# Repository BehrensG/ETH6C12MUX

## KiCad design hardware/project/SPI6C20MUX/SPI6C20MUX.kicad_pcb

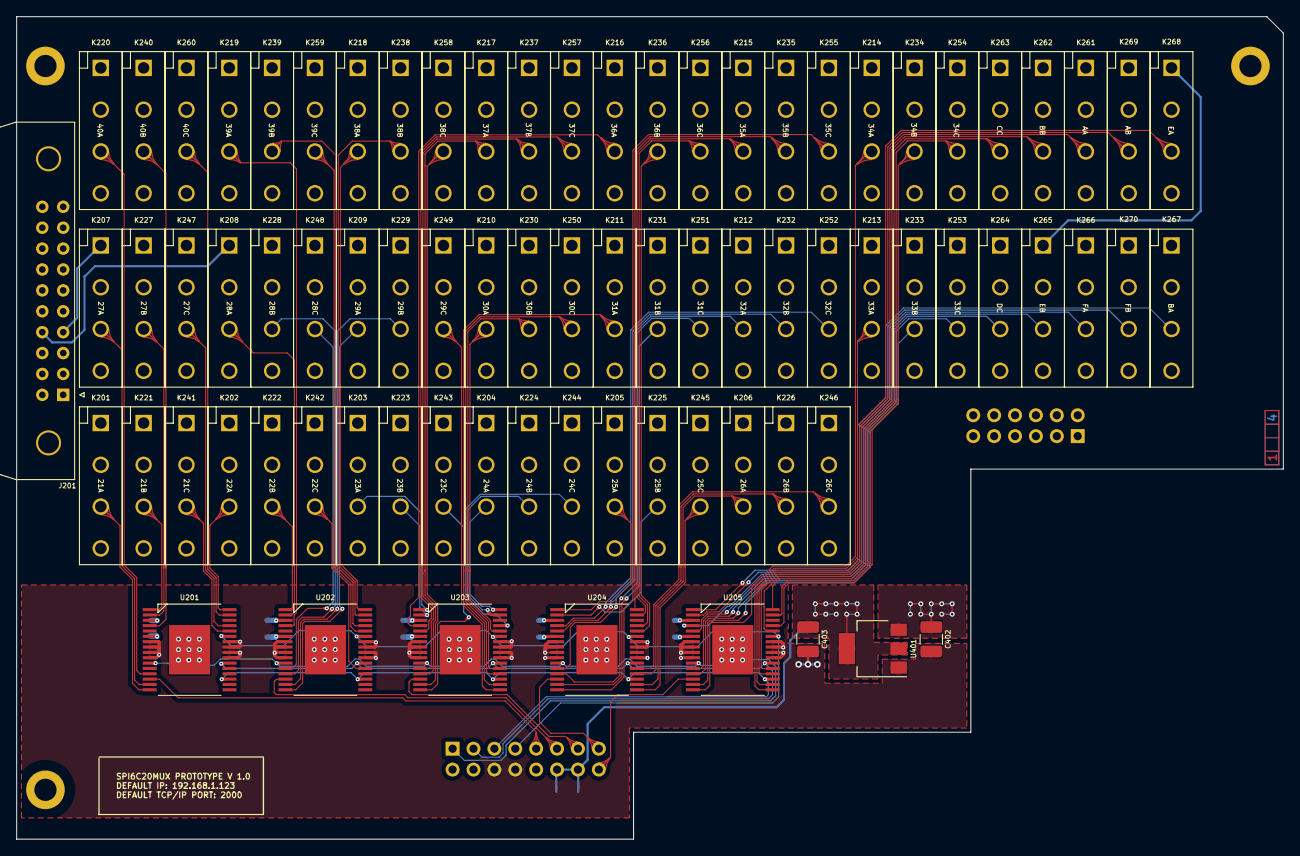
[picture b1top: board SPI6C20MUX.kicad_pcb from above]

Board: 4 copper layers, 154.0 x 100.0 mm, 98 parts (0 on the bottom side), 111 nets.

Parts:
C201, C202, C203, C204, C205, C206, C207, C208, C209, C210, C401, C404: 100n; C_0603_1608Metric_Pad1.05x0.95mm_HandSolder
C402, C403: 22u; C_1210_3225Metric_Pad1.42x2.65mm_HandSolder
H101, H102, H103: MountingHole; MountingHole_2.7mm_M2.5_DIN965_Pad
J201: 5499141-4; IDC-Header_2x10_P2.54mm_Horizontal_Lock
J301: Conn_02x06_Odd_Even; PinHeader_2x06_P2.54mm_Vertical
J302: Conn_02x08_Odd_Even; PinHeader_2x08_P2.54mm_Vertical
K201, K202, K203, K204, K205, K206, K207, K208, K209, K210, K211, K212, K213, K214, K215, K216, K217, K218, K219, K220, K221, K222, K223, K224, K225, K226, K227, K228, K229, K230, K231, K232, K233, K234, K235, K236, K237, K238, K239, K240, K241, K242, K243, K244, K245, K246, K247, K248, K249, K250, K251, K252, K253, K254, K255, K256, K257, K258, K259, K260, K261, K262, K263, K264, K265, K266, K267, K268, K269, K270: HE3621A0510; HE360_x-5331272-5
R301, R302: 10k; R_0603_1608Metric_Pad1.05x0.95mm_HandSolder
U201, U202, U203, U204, U205: MCZ33996; HSOP-32-1EP_7.5x11.0mm_P0.65mm_ThermalVias
U401: LM1117MPX-3.3; SOT-223-3_TabPin2

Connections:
+3V3: C201.1, C202.1, C203.1, C204.1, C205.1, C403.1, C404.1, J302.12, J302.14, R301.1, R302.1, U201.3, U202.3, U203.3, U204.3, U205.3, U401.2
+5V: C206.1, C207.1, C208.1, C209.1, C210.1, C401.1, C402.1, J302.2, J302.4, K201.2, K202.2, K203.2, K204.2, K205.2, K206.2, K207.2, K208.2, K209.2, K210.2, K211.2, K212.2, K213.2, K214.2, K215.2, K216.2, K217.2, K218.2, K219.2, K220.2, K221.2, K222.2, K223.2, K224.2, K225.2, K226.2, K227.2, K228.2, K229.2, K230.2, K231.2, K232.2, K233.2, K234.2, K235.2, K236.2, K237.2, K238.2, K239.2, K240.2, K241.2, K242.2, K243.2, K244.2, K245.2, K246.2, K247.2, K248.2, K249.2, K250.2, K251.2, K252.2, K253.2, K254.2, K255.2, K256.2, K257.2, K258.2, K259.2, K260.2, K261.2, K262.2, K263.2, K264.2, K265.2, K266.2, K267.2, K268.2, K269.2, K270.2, U201.6, U202.6, U203.6, U204.6, U205.6, U401.3
/Connector/A: J301.1, J301.2, K261.1, K269.1
/Connector/B: J301.3, J301.4, K262.1, K267.1
/Connector/C: J301.5, J301.6, K263.1
/Connector/D: J301.11, J301.12, K264.1
/Connector/E: J301.9, J301.10, K265.1, K268.1
/Connector/F: J301.7, J301.8, K266.1, K270.1
/Connector/RELAY2_SCLK: J302.1, U201.11, U202.11, U203.11, U204.11, U205.11
/Connector/RELAY2_SI: J302.5, U201.19, U202.19, U203.19, U204.19, U205.19
/Connector/RELAY2_SO: J302.3, U201.22, U202.22, U203.22, U204.22, U205.22
/Connector/RELAY2_~CS0: J302.9, U201.14
/Connector/RELAY2_~CS1: J302.11, U202.14
/Connector/RELAY2_~CS2: J302.13, U203.14
/Connector/RELAY2_~CS3: J302.15, U204.14
/Connector/RELAY2_~CS4: J302.16, U205.14
/Connector/RELAY2_~RST: J302.7, U201.27, U202.27, U203.27, U204.27, U205.27
/Relays/PIN21: J201.1, K201.1, K221.1, K241.1
/Relays/PIN21A: K201.4, K202.4, K203.4, K204.4, K205.4, K206.4, K207.4, K208.4, K209.4, K210.4, K211.4, K212.4, K213.4, K214.4, K215.4, K216.4, K217.4, K218.4, K219.4, K220.4, K261.4, K266.4, K267.4, K268.4
/Relays/PIN21B: K221.4, K222.4, K223.4, K224.4, K225.4, K226.4, K227.4, K228.4, K229.4, K230.4, K231.4, K232.4, K233.4, K234.4, K235.4, K236.4, K237.4, K238.4, K239.4, K240.4, K262.4, K265.4, K269.4, K270.4
/Relays/PIN21C: K241.4, K242.4, K243.4, K244.4, K245.4, K246.4, K247.4, K248.4, K249.4, K250.4, K251.4, K252.4, K253.4, K254.4, K255.4, K256.4, K257.4, K258.4, K259.4, K260.4, K263.4, K264.4
/Relays/PIN22: J201.2, K202.1, K222.1, K242.1
/Relays/PIN23: J201.3, K203.1, K223.1, K243.1
/Relays/PIN24: J201.4, K204.1, K224.1, K244.1
/Relays/PIN25: J201.5, K205.1, K225.1, K245.1
/Relays/PIN26: J201.6, K206.1, K226.1, K246.1
/Relays/PIN27: J201.7, K207.1, K227.1, K247.1
/Relays/PIN28: J201.8, K208.1, K228.1, K248.1
/Relays/PIN29: J201.9, K209.1, K229.1, K249.1
/Relays/PIN30: J201.10, K210.1, K230.1, K250.1
/Relays/PIN31: J201.11, K211.1, K231.1, K251.1
/Relays/PIN32: J201.12, K212.1, K232.1, K252.1
/Relays/PIN33: J201.13, K213.1, K233.1, K253.1
/Relays/PIN34: J201.14, K214.1, K234.1, K254.1
/Relays/PIN35: J201.15, K215.1, K235.1, K255.1
/Relays/PIN36: J201.16, K216.1, K236.1, K256.1
/Relays/PIN37: J201.17, K217.1, K237.1, K257.1
/Relays/PIN38: J201.18, K218.1, K238.1, K258.1
/Relays/PIN39: J201.19, K219.1, K239.1, K259.1
/Relays/PIN40: J201.20, K220.1, K240.1, K260.1
/Relays/RELAY21A: K201.3, U201.16
/Relays/RELAY21B: K221.3, U201.1
/Relays/RELAY21C: K241.3, U201.28
/Relays/RELAY22A: K202.3, U201.32
/Relays/RELAY22B: K222.3, U202.1
/Relays/RELAY22C: K242.3, U202.21
/Relays/RELAY23A: K203.3, U203.1
/Relays/RELAY23B: K223.3, U203.2
/Relays/RELAY23C: K243.3, U203.16
/Relays/RELAY24A: K204.3, U203.32
/Relays/RELAY24B: K224.3, U203.31
/Relays/RELAY24C: K244.3, U203.29
/Relays/RELAY25A: K205.3, U204.1
/Relays/RELAY25B: K225.3, U204.2
/Relays/RELAY25C: K245.3, U204.17
/Relays/RELAY26A: K206.3, U204.18
/Relays/RELAY26B: K226.3, U204.20
/Relays/RELAY26C: K246.3, U204.21
/Relays/RELAY27A: K207.3, U201.15
/Relays/RELAY27B: K227.3, U201.2
/Relays/RELAY27C: K247.3, U201.29
/Relays/RELAY28A: K208.3, U202.2
/Relays/RELAY28B: K228.3, U202.13
/Relays/RELAY28C: K248.3, U202.12
/Relays/RELAY29A: K209.3, U202.16
/Relays/RELAY29B: K229.3, U202.15
/Relays/RELAY29C: K249.3, U203.17
/Relays/RELAY30A: K210.3, U203.28
/Relays/RELAY30B: K230.3, U203.21
/Relays/RELAY30C: K250.3, U203.20
/Relays/RELAY31A: K211.3, U203.18
/Relays/RELAY31B: K231.3, U204.15
/Relays/RELAY31C: K251.3, U204.13
/Relays/RELAY32A: K212.3, U204.12
/Relays/RELAY32B: K232.3, U204.5
/Relays/RELAY32C: K252.3, U204.4
/Relays/RELAY33A: K213.3, U205.17
/Relays/RELAY33B: K233.3, U205.15
/Relays/RELAY33C: K253.3, U205.13
/Relays/RELAY34A: K214.3, U205.16
/Relays/RELAY34B: K234.3, U205.29
/Relays/RELAY34C: K254.3, U205.31
/Relays/RELAY35A: K215.3, U204.31
/Relays/RELAY35B: K235.3, U204.32
/Relays/RELAY35C: K255.3, U204.16
/Relays/RELAY36A: K216.3, U203.4
/Relays/RELAY36B: K236.3, U204.28
/Relays/RELAY36C: K256.3, U204.29
/Relays/RELAY37A: K217.3, U203.13
/Relays/RELAY37B: K237.3, U203.12
/Relays/RELAY37C: K257.3, U203.5
/Relays/RELAY38A: K218.3, U202.32
/Relays/RELAY38B: K238.3, U202.31
/Relays/RELAY38C: K258.3, U203.15
/Relays/RELAY39A: K219.3, U202.4
/Relays/RELAY39B: K239.3, U202.29
/Relays/RELAY39C: K259.3, U202.28
/Relays/RELAY40A: K220.3, U201.13
/Relays/RELAY40B: K240.3, U201.4
/Relays/RELAY40C: K260.3, U201.31
/Relays/RELAYA: K261.3, U205.21
/Relays/RELAYAB: K269.3, U205.20
/Relays/RELAYB: K262.3, U205.28
/Relays/RELAYBA: K267.3, U205.1
/Relays/RELAYC: K263.3, U205.32
/Relays/RELAYD: K264.3, U205.12
/Relays/RELAYE: K265.3, U205.5
/Relays/RELAYEA: K268.3, U205.18
/Relays/RELAYF: K266.3, U205.4
/Relays/RELAYFA: K270.3, U205.2
GND: C201.2, C202.2, C203.2, C204.2, C205.2, C206.2, C207.2, C208.2, C209.2, C210.2, C401.2, C402.2, C403.2, C404.2, J302.6, J302.8, R301.2, R302.2, U201.7, U201.8, U201.9, U201.10, U201.23, U201.24, U201.25, U201.26, U201.33, U202.7, U202.8, U202.9, U202.10, U202.23, U202.24, U202.25, U202.26, U202.33, U203.7, U203.8, U203.9, U203.10, U203.23, U203.24, U203.25, U203.26, U203.33, U204.7, U204.8, U204.9, U204.10, U204.23, U204.24, U204.25, U204.26, U204.33, U205.7, U205.8, U205.9, U205.10, U205.23, U205.24, U205.25, U205.26, U205.33, U401.1

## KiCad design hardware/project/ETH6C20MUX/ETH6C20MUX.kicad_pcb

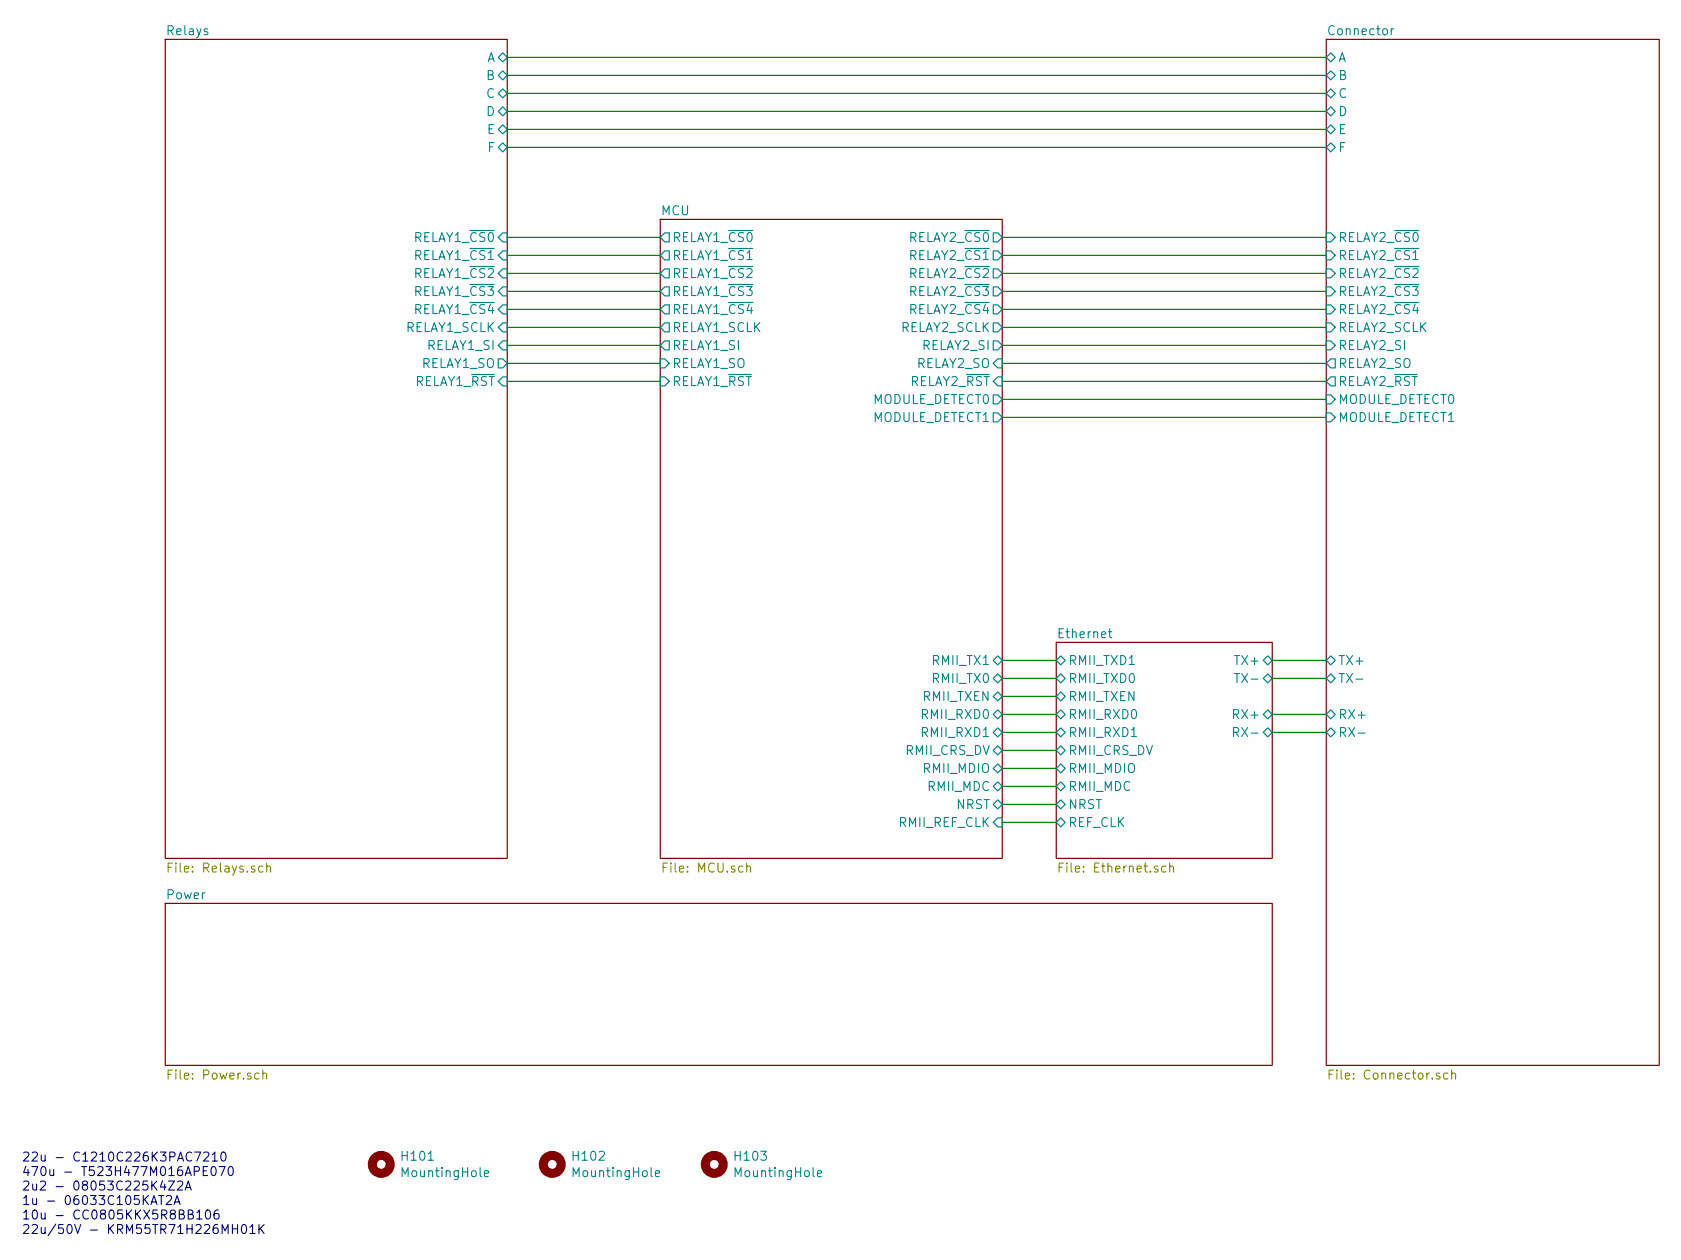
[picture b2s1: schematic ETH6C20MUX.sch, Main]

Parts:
H101, H102, H103: MountingHole; MountingHole_2.7mm_M2.5_DIN965_Pad

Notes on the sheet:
22u - C1210C226K3PAC7210 470u - T523H477M016APE070 2u2 - 08053C225K4Z2A 1u - 06033C105KAT2A 10u - CC0805KKX5R8BB106 22u/50V - KRM55TR71H226MH01K

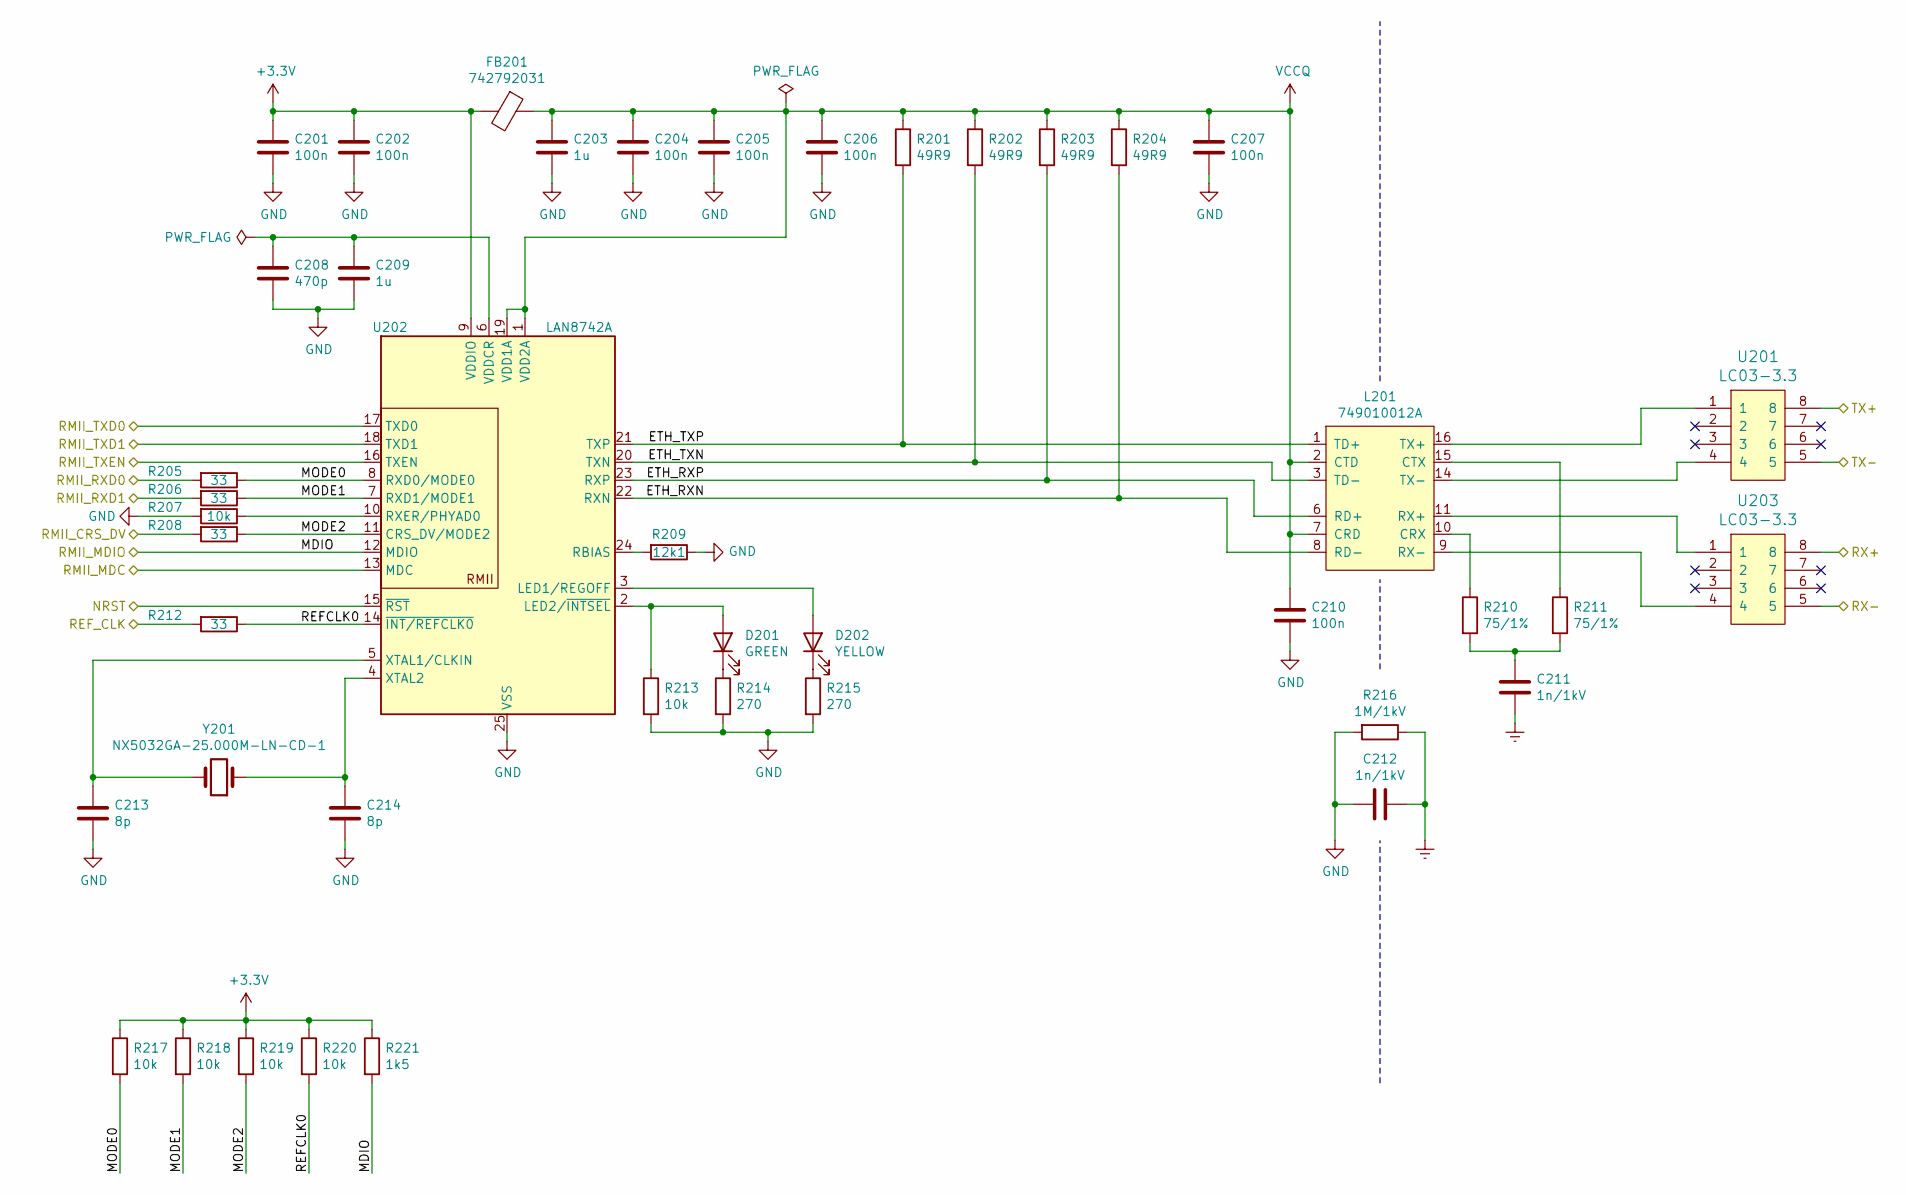
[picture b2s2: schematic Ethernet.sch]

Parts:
C201, C202, C204, C205, C206, C207, C210: 100n; C_0603_1608Metric_Pad1.08x0.95mm_HandSolder
C203, C209: 1u; C_0603_1608Metric_Pad1.08x0.95mm_HandSolder
C208: 470p; C_0603_1608Metric_Pad1.08x0.95mm_HandSolder
C211, C212: 1n/1kV; C_1206_3216Metric_Pad1.42x1.75mm_HandSolder
C213, C214: 8p; C_0603_1608Metric_Pad1.08x0.95mm_HandSolder
D201: GREEN; LED_0603_1608Metric_Pad1.05x0.95mm_HandSolder
D202: YELLOW; LED_0603_1608Metric_Pad1.05x0.95mm_HandSolder
FB201: 742792031; R_0805_2012Metric_Pad1.15x1.40mm_HandSolder
L201: 749010012A
R201, R202, R203, R204: 49R9; R_0603_1608Metric_Pad0.98x0.95mm_HandSolder
R205, R206, R208, R212: 33; R_0603_1608Metric_Pad0.98x0.95mm_HandSolder
R207, R213, R217, R218, R219, R220: 10k; R_0603_1608Metric_Pad0.98x0.95mm_HandSolder
R209: 12k1; R_0603_1608Metric_Pad0.98x0.95mm_HandSolder
R210, R211: 75/1%; R_0603_1608Metric_Pad0.98x0.95mm_HandSolder
R214, R215: 270; R_0603_1608Metric_Pad0.98x0.95mm_HandSolder
R216: 1M/1kV; R_1206_3216Metric_Pad1.30x1.75mm_HandSolder
R221: 1k5; R_0603_1608Metric_Pad0.98x0.95mm_HandSolder
U201, U203: LC03-3.3; SO8E
U202: LAN8742A; QFN-24-1EP_4x4mm_P0.5mm_EP2.6x2.6mm_ThermalVias
Y201: NX5032GA-25.000M-LN-CD-1; NX5032GA

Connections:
+3V3: C201.1, C202.1, FB201.2, R217.1, R218.1, R219.1, R220.1, R221.1, U202.9 (VDDIO); also elsewhere on the board
/Connector/RX+: U203.8; also elsewhere on the board
/Connector/RX-: U203.5; also elsewhere on the board
/Connector/TX+: U201.8; also elsewhere on the board
/Connector/TX-: U201.5; also elsewhere on the board
/Ethernet/ETH_RXN: L201.8 (RD-), R204.2, U202.22 (RXN)
/Ethernet/ETH_RXP: L201.6 (RD+), R203.2, U202.23 (RXP)
/Ethernet/ETH_TXN: L201.3 (TD-), R202.2, U202.20 (TXN)
/Ethernet/ETH_TXP: L201.1 (TD+), R201.2, U202.21 (TXP)
/Ethernet/MODE0: R205.1, R217.2, U202.8 (RXD0/MODE0)
/Ethernet/MODE1: R206.1, R218.2, U202.7 (RXD1/MODE1)
/Ethernet/MODE2: R208.1, R219.2, U202.11 (CRS_DV/MODE2)
/Ethernet/NRST: U202.15 (~RST); also elsewhere on the board
/Ethernet/REFCLK0: R212.1, R220.2, U202.14 (~INT/REFCLK0)
/Ethernet/REF_CLK: R212.2; also elsewhere on the board
/Ethernet/RMII_CRS_DV: R208.2; also elsewhere on the board
/Ethernet/RMII_MDC: U202.13 (MDC); also elsewhere on the board
/Ethernet/RMII_MDIO: R221.2, U202.12 (MDIO); also elsewhere on the board
/Ethernet/RMII_RXD0: R205.2; also elsewhere on the board
/Ethernet/RMII_RXD1: R206.2; also elsewhere on the board
/Ethernet/RMII_TXEN: U202.16 (TXEN); also elsewhere on the board
/MCU/RMII_TX0: U202.17 (TXD0); also elsewhere on the board
/MCU/RMII_TX1: U202.18 (TXD1); also elsewhere on the board
Earth: C211.2, C212.1, R216.1; also elsewhere on the board
GND: C201.2, C202.2, C203.2, C204.2, C205.2, C206.2, C207.2, C208.2, C209.2, C210.2, C212.2, C213.2, C214.2, R207.2, R209.1, R213.2, R214.2, R215.2, R216.2, U202.25 (VSS); also elsewhere on the board
unnamed: C208.1, C209.1, U202.6 (VDDCR)
unnamed: C211.1, R210.2, R211.2
unnamed: C213.1, U202.5 (XTAL1/CLKIN), Y201.2
unnamed: C214.1, U202.4 (XTAL2), Y201.1
unnamed: D201.1 (K), R214.1
unnamed: D201.2 (A), R213.1, U202.2 (LED2/~INTSEL)
unnamed: D202.1 (K), R215.1
unnamed: D202.2 (A), U202.3 (LED1/REGOFF)
unnamed: L201.9 (RX-), U203.4
unnamed: L201.10 (CRX), R210.1
unnamed: L201.11 (RX+), U203.1
unnamed: L201.14 (TX-), U201.4
unnamed: L201.15 (CTX), R211.1
unnamed: L201.16 (TX+), U201.1
unnamed: R207.1, U202.10 (RXER/PHYAD0)
unnamed: R209.2, U202.24 (RBIAS)
VCCQ: C203.1, C204.1, C205.1, C206.1, C207.1, C210.1, FB201.1, L201.2 (CTD), L201.7 (CRD), R201.1, R202.1, R203.1, R204.1, U202.1 (VDD2A), U202.19 (VDD1A)

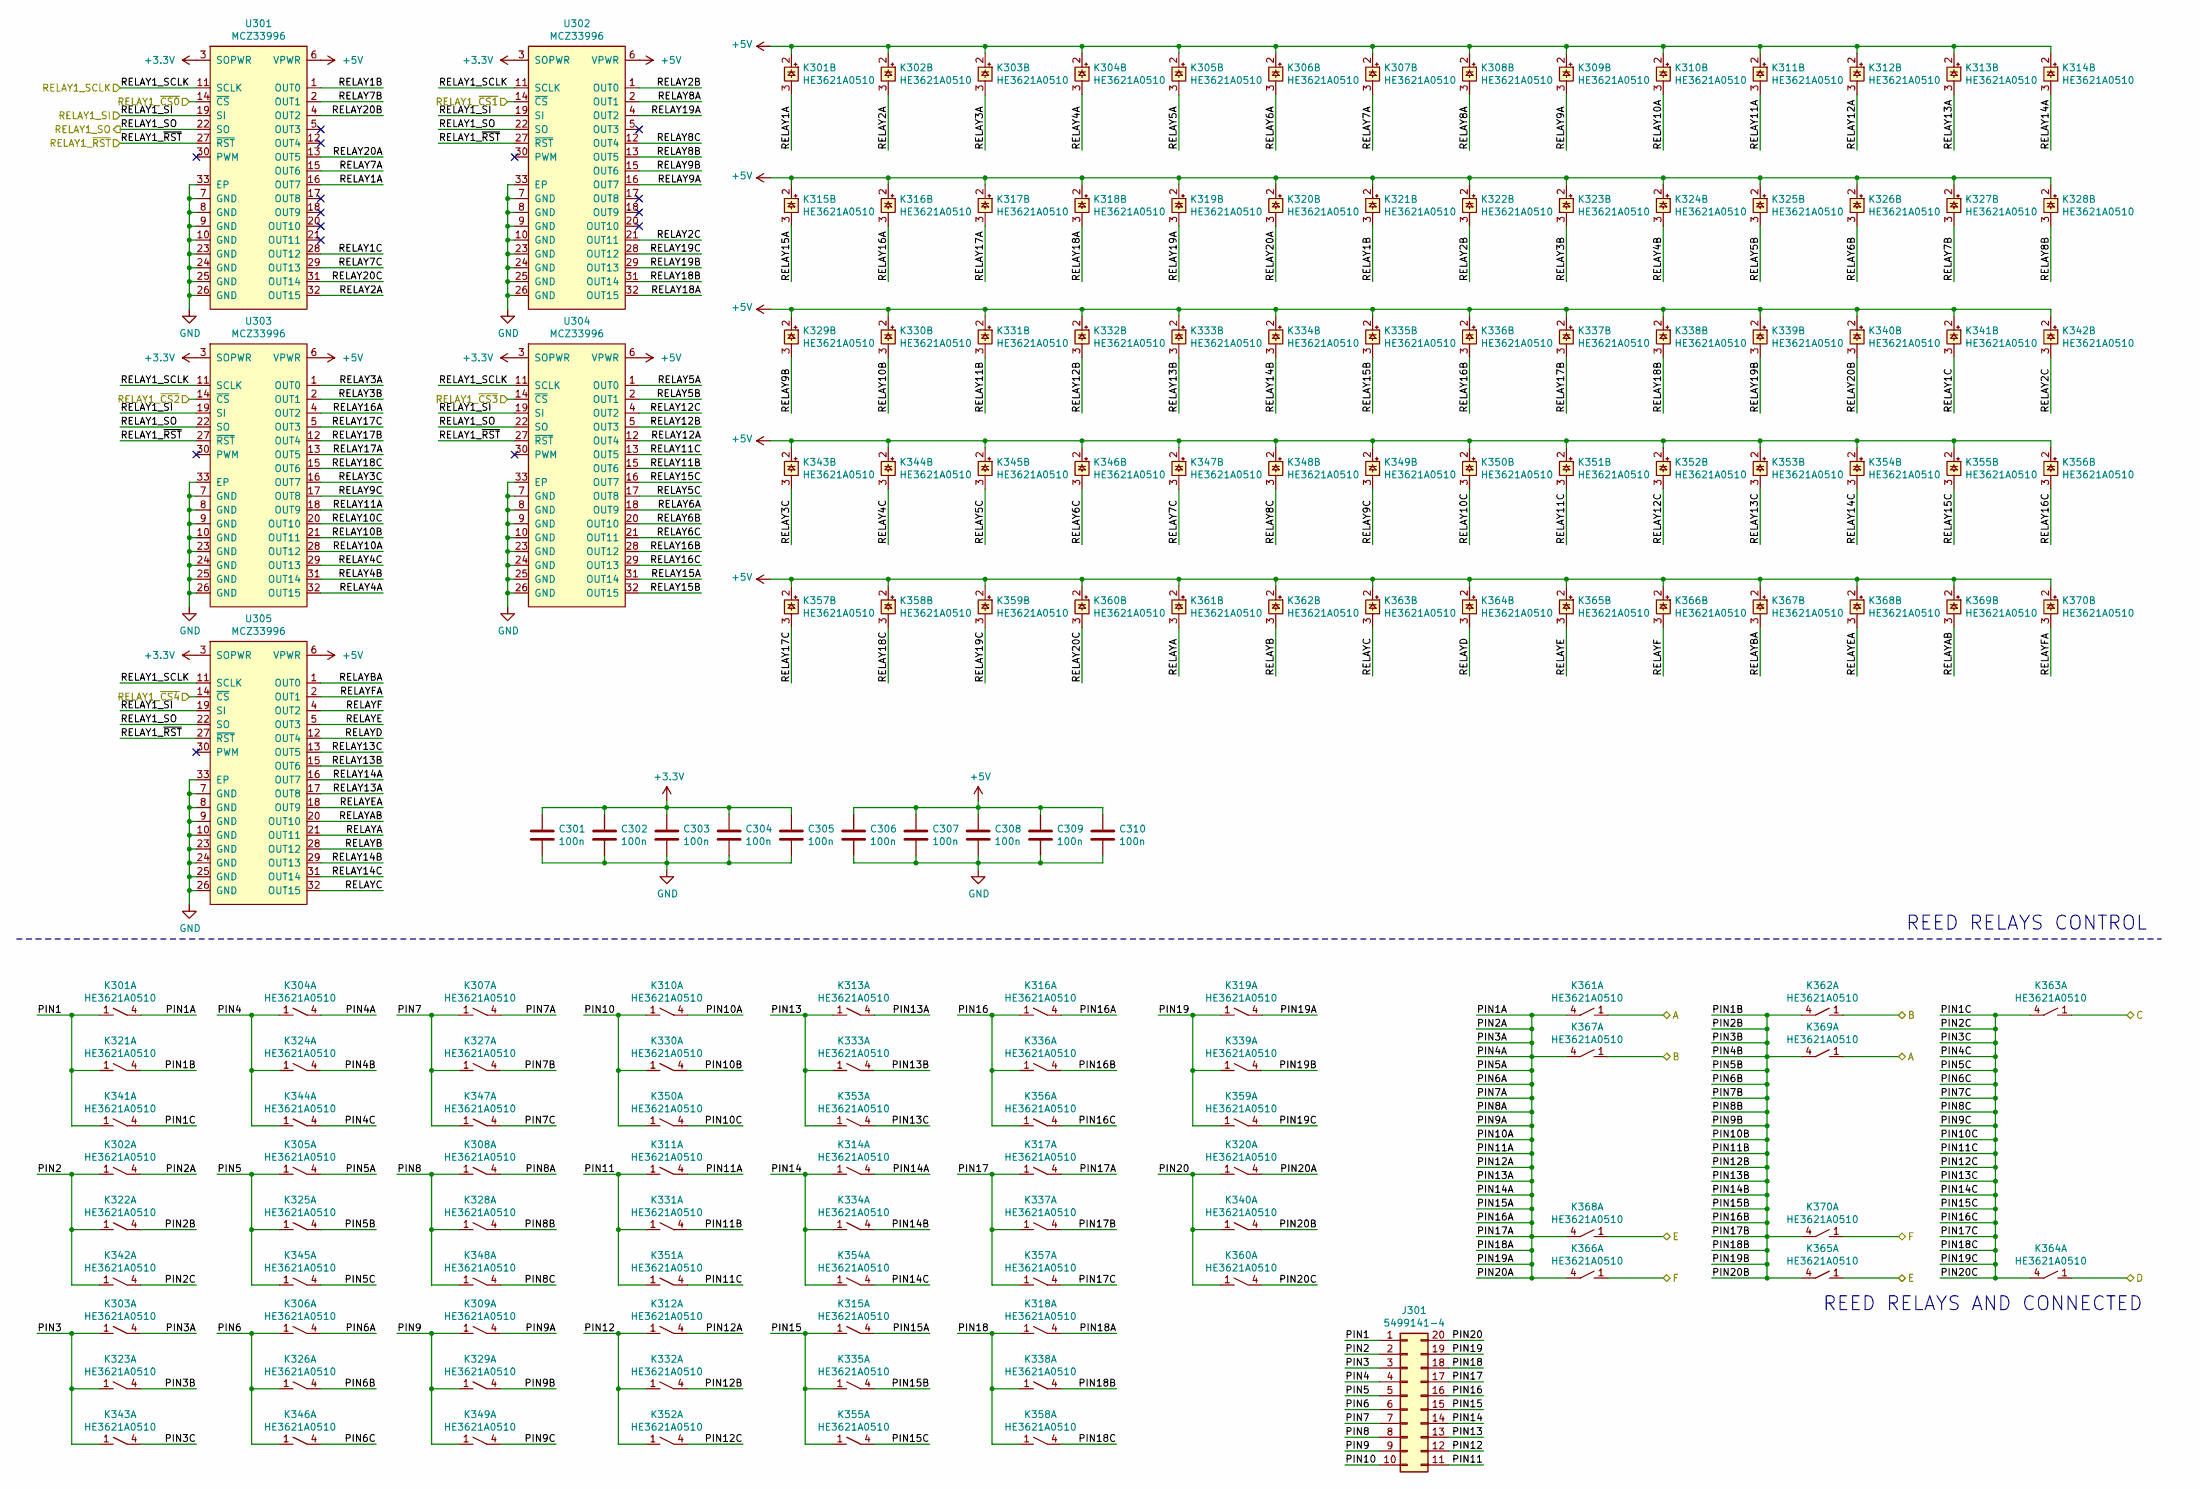
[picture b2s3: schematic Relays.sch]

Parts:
C301, C302, C303, C304, C305, C306, C307, C308, C309, C310: 100n; C_0603_1608Metric_Pad1.08x0.95mm_HandSolder
J301: 5499141-4; IDC-Header_2x10_P2.54mm_Horizontal_Lock
K301, K302, K303, K304, K305, K306, K307, K308, K309, K310, K311, K312, K313, K314, K315, K316, K317, K318, K319, K320, K321, K322, K323, K324, K325, K326, K327, K328, K329, K330, K331, K332, K333, K334, K335, K336, K337, K338, K339, K340, K341, K342, K343, K344, K345, K346, K347, K348, K349, K350, K351, K352, K353, K354, K355, K356, K357, K358, K359, K360, K361, K362, K363, K364, K365, K366, K367, K368, K369, K370: HE3621A0510; HE360_x-5050462-8
U301, U302, U303, U304, U305: MCZ33996; HSOP-32-1EP_7.5x11.0mm_P0.65mm_ThermalVias

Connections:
+3V3: C301.1, C302.1, C303.1, C304.1, C305.1, U301.3 (SOPWR), U302.3 (SOPWR), U303.3 (SOPWR), U304.3 (SOPWR), U305.3 (SOPWR); also elsewhere on the board
+5V: C306.1, C307.1, C308.1, C309.1, C310.1, K301.2, K302.2, K303.2, K304.2, K305.2, K306.2, K307.2, K308.2, K309.2, K310.2, K311.2, K312.2, K313.2, K314.2, K315.2, K316.2, K317.2, K318.2, K319.2, K320.2, K321.2, K322.2, K323.2, K324.2, K325.2, K326.2, K327.2, K328.2, K329.2, K330.2, K331.2, K332.2, K333.2, K334.2, K335.2, K336.2, K337.2, K338.2, K339.2, K340.2, K341.2, K342.2, K343.2, K344.2, K345.2, K346.2, K347.2, K348.2, K349.2, K350.2, K351.2, K352.2, K353.2, K354.2, K355.2, K356.2, K357.2, K358.2, K359.2, K360.2, K361.2, K362.2, K363.2, K364.2, K365.2, K366.2, K367.2, K368.2, K369.2, K370.2, U301.6 (VPWR), U302.6 (VPWR), U303.6 (VPWR), U304.6 (VPWR), U305.6 (VPWR); also elsewhere on the board
/Connector/A: K361.1, K369.1; also elsewhere on the board
/Connector/B: K362.1, K367.1; also elsewhere on the board
/Connector/C: K363.1; also elsewhere on the board
/Connector/D: K364.1; also elsewhere on the board
/Connector/E: K365.1, K368.1; also elsewhere on the board
/Connector/F: K366.1, K370.1; also elsewhere on the board
/MCU/RELAY1_SCLK: U301.11 (SCLK), U302.11 (SCLK), U303.11 (SCLK), U304.11 (SCLK), U305.11 (SCLK); also elsewhere on the board
/MCU/RELAY1_SI: U301.19 (SI), U302.19 (SI), U303.19 (SI), U304.19 (SI), U305.19 (SI); also elsewhere on the board
/MCU/RELAY1_SO: U301.22 (SO), U302.22 (SO), U303.22 (SO), U304.22 (SO), U305.22 (SO); also elsewhere on the board
/MCU/RELAY1_~CS0: U301.14 (~CS); also elsewhere on the board
/MCU/RELAY1_~CS1: U302.14 (~CS); also elsewhere on the board
/MCU/RELAY1_~CS2: U303.14 (~CS); also elsewhere on the board
/MCU/RELAY1_~CS3: U304.14 (~CS); also elsewhere on the board
/MCU/RELAY1_~CS4: U305.14 (~CS); also elsewhere on the board
/MCU/RELAY1_~RST: U301.27 (~RST), U302.27 (~RST), U303.27 (~RST), U304.27 (~RST), U305.27 (~RST); also elsewhere on the board
/Relays/PIN1: J301.1, K301.1, K321.1, K341.1
/Relays/PIN2: J301.2, K302.1, K322.1, K342.1
/Relays/PIN3: J301.3, K303.1, K323.1, K343.1
/Relays/PIN4: J301.4, K304.1, K324.1, K344.1
/Relays/PIN5: J301.5, K305.1, K325.1, K345.1
/Relays/PIN6: J301.6, K306.1, K326.1, K346.1
/Relays/PIN7: J301.7, K307.1, K327.1, K347.1
/Relays/PIN8: J301.8, K308.1, K328.1, K348.1
/Relays/PIN9: J301.9, K309.1, K329.1, K349.1
/Relays/PIN10: J301.10, K310.1, K330.1, K350.1
/Relays/PIN10A: K301.4, K302.4, K303.4, K304.4, K305.4, K306.4, K307.4, K308.4, K309.4, K310.4, K311.4, K312.4, K313.4, K314.4, K315.4, K316.4, K317.4, K318.4, K319.4, K320.4, K361.4, K366.4, K367.4, K368.4
/Relays/PIN10B: K321.4, K322.4, K323.4, K324.4, K325.4, K326.4, K327.4, K328.4, K329.4, K330.4, K331.4, K332.4, K333.4, K334.4, K335.4, K336.4, K337.4, K338.4, K339.4, K340.4, K362.4, K365.4, K369.4, K370.4
/Relays/PIN10C: K341.4, K342.4, K343.4, K344.4, K345.4, K346.4, K347.4, K348.4, K349.4, K350.4, K351.4, K352.4, K353.4, K354.4, K355.4, K356.4, K357.4, K358.4, K359.4, K360.4, K363.4, K364.4
/Relays/PIN11: J301.11, K311.1, K331.1, K351.1
/Relays/PIN12: J301.12, K312.1, K332.1, K352.1
/Relays/PIN13: J301.13, K313.1, K333.1, K353.1
/Relays/PIN14: J301.14, K314.1, K334.1, K354.1
/Relays/PIN15: J301.15, K315.1, K335.1, K355.1
/Relays/PIN16: J301.16, K316.1, K336.1, K356.1
/Relays/PIN17: J301.17, K317.1, K337.1, K357.1
/Relays/PIN18: J301.18, K318.1, K338.1, K358.1
/Relays/PIN19: J301.19, K319.1, K339.1, K359.1
/Relays/PIN20: J301.20, K320.1, K340.1, K360.1
/Relays/RELAY1A: K301.3, U301.16 (OUT7)
/Relays/RELAY1B: K321.3, U301.1 (OUT0)
/Relays/RELAY1C: K341.3, U301.28 (OUT12)
/Relays/RELAY2A: K302.3, U301.32 (OUT15)
/Relays/RELAY2B: K322.3, U302.1 (OUT0)
/Relays/RELAY2C: K342.3, U302.21 (OUT11)
/Relays/RELAY3A: K303.3, U303.1 (OUT0)
/Relays/RELAY3B: K323.3, U303.2 (OUT1)
/Relays/RELAY3C: K343.3, U303.16 (OUT7)
/Relays/RELAY4A: K304.3, U303.32 (OUT15)
/Relays/RELAY4B: K324.3, U303.31 (OUT14)
/Relays/RELAY4C: K344.3, U303.29 (OUT13)
/Relays/RELAY5A: K305.3, U304.1 (OUT0)
/Relays/RELAY5B: K325.3, U304.2 (OUT1)
/Relays/RELAY5C: K345.3, U304.17 (OUT8)
/Relays/RELAY6A: K306.3, U304.18 (OUT9)
/Relays/RELAY6B: K326.3, U304.20 (OUT10)
/Relays/RELAY6C: K346.3, U304.21 (OUT11)
/Relays/RELAY7A: K307.3, U301.15 (OUT6)
/Relays/RELAY7B: K327.3, U301.2 (OUT1)
/Relays/RELAY7C: K347.3, U301.29 (OUT13)
/Relays/RELAY8A: K308.3, U302.2 (OUT1)
/Relays/RELAY8B: K328.3, U302.13 (OUT5)
/Relays/RELAY8C: K348.3, U302.12 (OUT4)
/Relays/RELAY9A: K309.3, U302.16 (OUT7)
/Relays/RELAY9B: K329.3, U302.15 (OUT6)
/Relays/RELAY9C: K349.3, U303.17 (OUT8)
/Relays/RELAY10A: K310.3, U303.28 (OUT12)
/Relays/RELAY10B: K330.3, U303.21 (OUT11)
/Relays/RELAY10C: K350.3, U303.20 (OUT10)
/Relays/RELAY11A: K311.3, U303.18 (OUT9)
/Relays/RELAY11B: K331.3, U304.15 (OUT6)
/Relays/RELAY11C: K351.3, U304.13 (OUT5)
/Relays/RELAY12A: K312.3, U304.12 (OUT4)
/Relays/RELAY12B: K332.3, U304.5 (OUT3)
/Relays/RELAY12C: K352.3, U304.4 (OUT2)
/Relays/RELAY13A: K313.3, U305.17 (OUT8)
/Relays/RELAY13B: K333.3, U305.15 (OUT6)
/Relays/RELAY13C: K353.3, U305.13 (OUT5)
/Relays/RELAY14A: K314.3, U305.16 (OUT7)
/Relays/RELAY14B: K334.3, U305.29 (OUT13)
/Relays/RELAY14C: K354.3, U305.31 (OUT14)
/Relays/RELAY15A: K315.3, U304.31 (OUT14)
/Relays/RELAY15B: K335.3, U304.32 (OUT15)
/Relays/RELAY15C: K355.3, U304.16 (OUT7)
/Relays/RELAY16A: K316.3, U303.4 (OUT2)
/Relays/RELAY16B: K336.3, U304.28 (OUT12)
/Relays/RELAY16C: K356.3, U304.29 (OUT13)
/Relays/RELAY17A: K317.3, U303.13 (OUT5)
/Relays/RELAY17B: K337.3, U303.12 (OUT4)
/Relays/RELAY17C: K357.3, U303.5 (OUT3)
/Relays/RELAY18A: K318.3, U302.32 (OUT15)
/Relays/RELAY18B: K338.3, U302.31 (OUT14)
/Relays/RELAY18C: K358.3, U303.15 (OUT6)
/Relays/RELAY19A: K319.3, U302.4 (OUT2)
/Relays/RELAY19B: K339.3, U302.29 (OUT13)
/Relays/RELAY19C: K359.3, U302.28 (OUT12)
/Relays/RELAY20A: K320.3, U301.13 (OUT5)
/Relays/RELAY20B: K340.3, U301.4 (OUT2)
/Relays/RELAY20C: K360.3, U301.31 (OUT14)
/Relays/RELAYA: K361.3, U305.21 (OUT11)
/Relays/RELAYAB: K369.3, U305.20 (OUT10)
/Relays/RELAYB: K362.3, U305.28 (OUT12)
/Relays/RELAYBA: K367.3, U305.1 (OUT0)
/Relays/RELAYC: K363.3, U305.32 (OUT15)
/Relays/RELAYD: K364.3, U305.12 (OUT4)
/Relays/RELAYE: K365.3, U305.5 (OUT3)
/Relays/RELAYEA: K368.3, U305.18 (OUT9)
/Relays/RELAYF: K366.3, U305.4 (OUT2)
/Relays/RELAYFA: K370.3, U305.2 (OUT1)
GND: C301.2, C302.2, C303.2, C304.2, C305.2, C306.2, C307.2, C308.2, C309.2, C310.2, U301.7 (GND), U301.8 (GND), U301.9 (GND), U301.10 (GND), U301.23 (GND), U301.24 (GND), U301.25 (GND), U301.26 (GND), U301.33 (EP), U302.7 (GND), U302.8 (GND), U302.9 (GND), U302.10 (GND), U302.23 (GND), U302.24 (GND), U302.25 (GND), U302.26 (GND), U302.33 (EP), U303.7 (GND), U303.8 (GND), U303.9 (GND), U303.10 (GND), U303.23 (GND), U303.24 (GND), U303.25 (GND), U303.26 (GND), U303.33 (EP), U304.7 (GND), U304.8 (GND), U304.9 (GND), U304.10 (GND), U304.23 (GND), U304.24 (GND), U304.25 (GND), U304.26 (GND), U304.33 (EP), U305.7 (GND), U305.8 (GND), U305.9 (GND), U305.10 (GND), U305.23 (GND), U305.24 (GND), U305.25 (GND), U305.26 (GND), U305.33 (EP); also elsewhere on the board

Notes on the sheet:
REED RELAYS AND CONNECTED
REED RELAYS CONTROL

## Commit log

2019-09-01 Added Power, MCU, FPGA, Relays, Ethernet, USB and Connector schematics. Created schematic library.
2019-09-02 Schematic design
2019-09-03 USB update
2019-09-05 FPGA schematic
2019-09-08 PCB design, need to redesign of the board to board connectors.
2019-09-08 PCB layout, board to board connector changed.
2019-09-08 PCB layout, deleted USB.
2019-09-12 Deleted FPGA part and change it for SPI IO chips. Change power supply circuit.
2019-09-22 Ranamed project to ETH6C20MUX. Added 4 channels. Schematic redesign and PCB layout.
2019-09-22 PCB done.
2019-09-23 Updated PCB. Added 3D components. Started BOM list.
2019-09-25 Gerber generated.
2019-09-25 All 3d models are present in PCB.
2019-10-02 Added SPI6C20MUX PCB module, part of ETH6C20MUX.
2019-10-03 SPI6C20MUX layout done, bug fixes in ETH6C20MUX layout.
2019-10-08 Bug fix in TSR2 2450 footprint.
2019-10-27 Added firmware software, based on zephyr OS.
2019-11-09 Small updates in PCB design.
2019-11-26 SPI module PCB modifications.
2019-12-01 Lwip ping works.
2019-12-01 Removed debug files
2019-12-02 Software development
2019-12-08 Software development. SPI flash write/read works correctly.
2019-12-12 SCPI commands development.
2019-12-13 Software development.
2019-12-19 Software and hardware development
2019-12-19 Cleaned object files
2019-12-22 Added http code, from code generator.
2019-12-24 Disabled fs.c file and deletect DHCP support. Resoterd main.h and updated scpi commands code.
2019-12-26 Small software changes
2019-12-28 Bug fix in SCPI_CreateSPICommands
2020-01-10 Bug fixes in software, still problem with relay index control.
2020-03-06 `vallen` is verified to be less than `len`, therefore, it can never be the case that `vallen >= len + sizeof(rhostname)`.
    This PR fixes the check so the `rhostname` array does not overflow.
    Reported-by: Github Security Lab <securitylab@github.com>
2020-04-18 Added pin swap for A,B,E and F.
2021-02-07 PCB redesign
2021-02-08 PCB design
2021-02-09 PCB layout
2021-02-11 Main PCB layout done
2021-02-11 Modifications in PCB main board.
2021-02-13 PCB main and module layout.
2021-02-13 PCB layouts done.
2021-02-14 Added FreeRTOS, and fix the bugs in relay switching.
2021-03-21 PCB modifications.
2024-07-08 README.md
